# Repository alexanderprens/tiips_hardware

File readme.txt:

This repository contains all code and design files for the TIIPS senior design project by Alexander Rens and Nile Morecraft, completed May 2017.
located at: https://github.com/alexanderprens/tiips_hardware

The folders contain:
	android app - .APK file for installing the TIIPS app
	barcodes - completed barcode designs and qr codes
	bluetooth code - code for the SiLabs BGM111 modules
	case files - STL files for the case
	pcb files - files for the PCB designs

Another repository contains the code for the Android application
located at: https://github.com/alexanderprens/tiips_android

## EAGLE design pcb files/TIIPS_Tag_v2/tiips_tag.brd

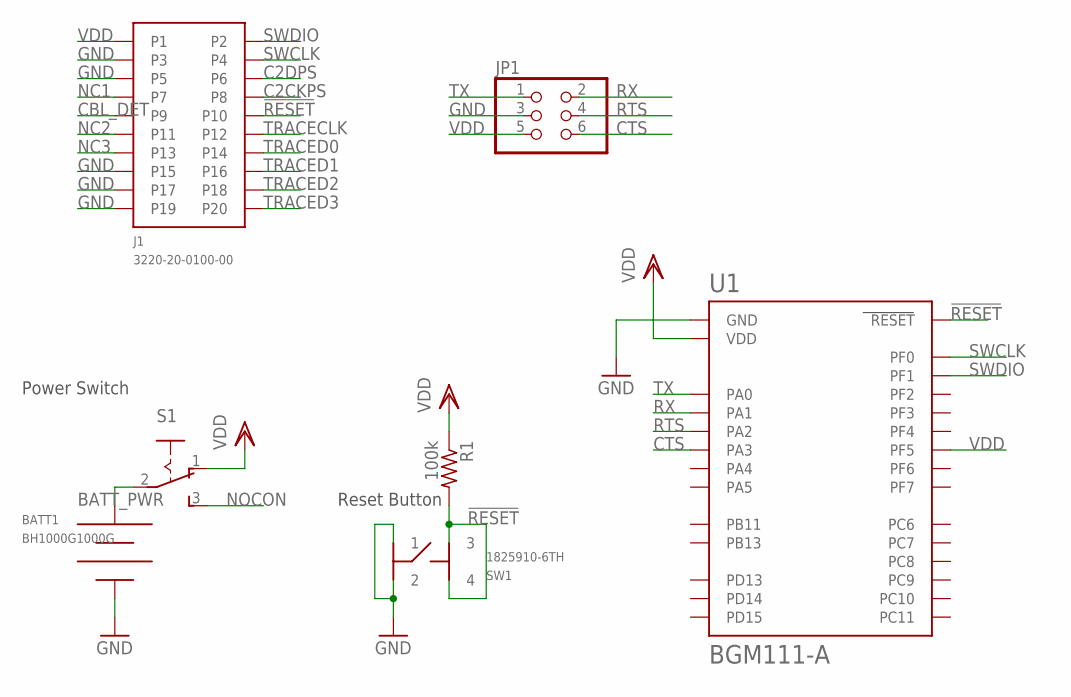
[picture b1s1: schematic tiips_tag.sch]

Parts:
BATT1: BH1000G1000G; BH
J1: 3220-20-0100-00
JP1: PINHD-2X3; 2X03
R1: 100k; 0309/10
S1: M251
SW1: 1825910-6TH; 1825910-6
U1: BGM111-A

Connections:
!RESET: J1.P10, R1.2, SW1.3, SW1.4, U1.RESET
BATT_PWR: BATT1.2 (3V), S1.2
C2CKPS: J1.P8
C2DPS: J1.P6
CBL_DET: J1.P9
CTS: JP1.6, U1.PA3
GND: BATT1.1 (GND), J1.P3, J1.P5, J1.P15, J1.P17, J1.P19, JP1.3, SW1.1, SW1.2, U1.GND, U1.GND@2 (GND), U1.GND@3 (GND), U1.GND@4 (GND)
NC1: J1.P7
NC2: J1.P11
NC3: J1.P13
NOCON: S1.3 (S)
RTS: JP1.4, U1.PA2
RX: JP1.2, U1.PA1
SWCLK: J1.P4, U1.PF0
SWDIO: J1.P2, U1.PF1
TRACECLK: J1.P12
TRACED0: J1.P14
TRACED1: J1.P16
TRACED2: J1.P18
TRACED3: J1.P20
TX: JP1.1, U1.PA0
VDD: J1.P1, JP1.5, R1.1, S1.1 (O), U1.PF5, U1.VDD

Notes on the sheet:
Power Switch
Reset Button

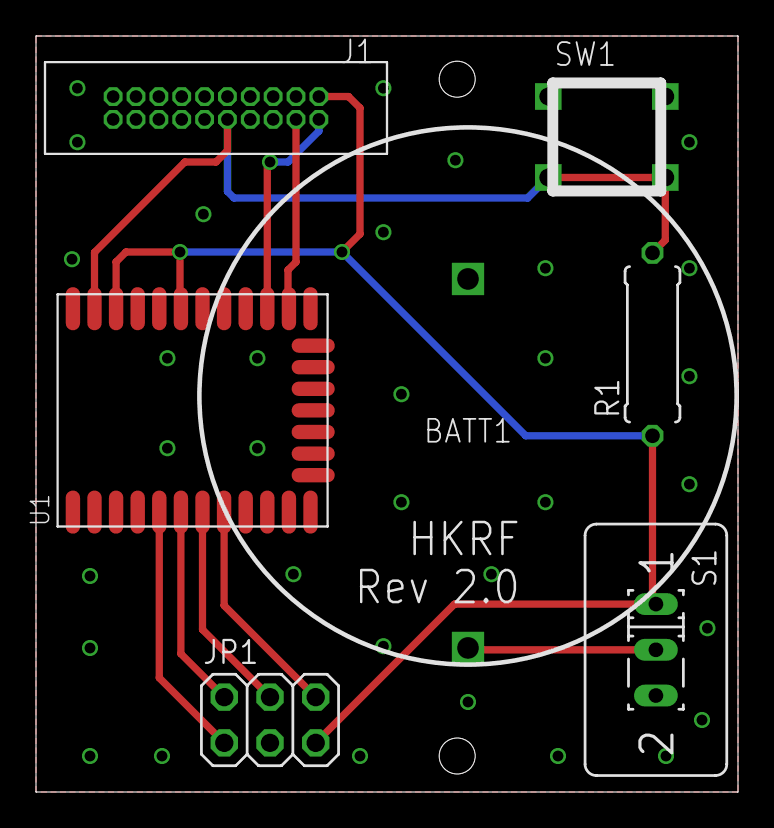
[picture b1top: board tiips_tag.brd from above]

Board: 2 copper layers, 39.0 x 42.0 mm, 7 parts (0 on the bottom side), 10 nets.

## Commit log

2017-04-16 added pcb files and bgm code files. changed master and tags to remove uart & clean changed master to do only battery voltage and missing, now 11 tags
2017-04-26 added case files updated to most recent ble code
2017-04-27 updated beacon and tag code with missing tag fixes added apk file for app
2017-05-01 updated apk from crash mistake updated beacon master to use 12 hour timer
2017-05-02 added barcodes to repo
2017-05-02 removed test button from view inventory
2017-05-04 added old version of bgm files changed folder names to be more descriptive added readme file
